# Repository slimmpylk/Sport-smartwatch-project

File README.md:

# Sportwatch

**A personal end-to-end smart/sport watch engineering project — custom electronics, PCB design, embedded software and system integration.**

This project is my attempt to design and build a complete sport-focused smartwatch from the ground up rather than assembling an existing development platform.

I am responsible for the full engineering workflow: component selection, datasheet analysis, schematic design, PCB architecture and layout, power design, sensor integration, RF-related design decisions, hardware bring-up, and eventually the embedded software running on the device.

> **Current phase:** hardware development. The schematic architecture is being designed in KiCad and the PCB will follow. Firmware and higher-level software development will begin as the hardware reaches the bring-up stage.

---

## Project goals

The goal is to build a compact wearable platform capable of supporting the core functions expected from a modern sport watch, while using the project as a practical system-level embedded engineering exercise.

The design includes:

- low-power application processor
- battery charging and power management
- AMOLED display
- GNSS
- inertial sensing
- magnetometer
- barometric pressure / altitude sensing
- temperature sensing
- ambient light sensing
- optical heart-rate / PPG hardware
- non-volatile storage
- haptic feedback
- wireless / RF subsystem
- physical buttons, charging and debug interfaces

The project is intentionally developed at component and PCB level rather than around a ready-made smartwatch module.

---

## Hardware architecture

| Subsystem | Main components / focus |
|---|---|
| Application processor | Ambiq Apollo510B |
| Power | Nordic nPM1300 PMIC |
| Display | RM69330-based round AMOLED |
| Motion | ST LSM6DSV16X IMU |
| Magnetometer | Bosch BMM350 |
| Pressure / altitude | Bosch BMP585 |
| Temperature | MAX30208 |
| Ambient light | OPT4001 |
| Optical sensing | MAX86140 / MAX86141 with discrete optical components |
| GNSS | u-blox MAX-F10S |
| Storage | eMMC |
| Haptics | TI DRV2625 |

Component choices and interfaces are verified against manufacturer datasheets as the design progresses.

### Display subsystem

Schematic excerpt for the round AMOLED display module interface (24-pin ZC-A1D43W-046 assembly): QSPI configuration, I²C touch controller, power rails and reset/enable circuitry:

---

## KiCad design organization

The schematic is divided into functional hierarchical sheets so each subsystem can be developed and reviewed independently.

```text
sportwatch_revA/
├── 01_APOLLO510B.kicad_sch
├── 02_POWER.kicad_sch
├── 03_DISPLAY.kicad_sch
├── 04_PPG.kicad_sch
├── 05_GNSS.kicad_sch
├── 06_WIFI.kicad_sch
├── 07_MOTION.kicad_sch
├── 08_ENVIRONMENT.kicad_sch
├── 09_STORAGE.kicad_sch
├── 10_HAPTICS.kicad_sch
├── 11_BUTTONS.kicad_sch
├── 12_CHARGING.kicad_sch
├── 13_DEBUG.kicad_sch
├── 14_RF.kicad_sch
├── sportwatch_revA.kicad_sch
├── sportwatch_revA.kicad_pcb
├── sportwatch_revA.kicad_pro
├── fp-lib-table
├── sym-lib-table
├── images/
│   └── display.jpg
└── libraries/
```

Custom symbols and footprints are kept with the project so the design remains portable between machines.

---

## Engineering focus

This project is primarily intended to demonstrate practical embedded hardware and system engineering, including:

- schematic capture and PCB design in **KiCad**
- reading and applying semiconductor datasheets
- component selection and interface design
- power-tree and battery-powered system design
- SPI / I²C and other digital interfaces
- mixed-signal sensor integration
- optical sensing / PPG subsystem design
- GNSS and RF integration
- decoupling, grounding and power-integrity considerations
- footprint verification against mechanical package drawings
- hierarchical schematic architecture
- hardware/software interface planning
- design validation before PCB manufacture
- Git-based engineering workflow and documentation

---

## Current development status

### Hardware

- [x] System architecture divided into functional schematic sheets
- [x] Initial power subsystem design
- [x] Application processor integration started
- [x] Motion-sensor integration
- [x] Custom symbols and footprints integrated where required
- [ ] Complete remaining schematic subsystems
- [ ] Full ERC and design review
- [ ] PCB placement
- [ ] PCB routing
- [ ] RF/layout review
- [ ] DRC and manufacturing review
- [ ] Prototype fabrication
- [ ] Hardware bring-up

### Software

Software development will follow the hardware bring-up phase.

Planned work includes:

- board-support and low-level drivers
- sensor acquisition
- power management
- display/UI integration
- GNSS handling
- activity and sport-related data processing
- storage
- device communications
- test and diagnostic tooling

The software side will be developed as part of the same project rather than treated as a separate pre-built platform.

---

## Development philosophy

The project is built around a simple principle: **understand and own the complete system**.

Rather than limiting the work to one layer, I want to work across the boundary between electronics and software — from component datasheets and PCB connectivity to low-level embedded code and final device behaviour.

That means the project evolves through the same stages as a real embedded product:

**requirements → architecture → schematic → PCB → prototype → bring-up → firmware → system integration → testing**

---

## Status

This repository is a work in progress and reflects an actively developed engineering project. The current focus is the PCB and electronics design phase, so incomplete sheets, un-routed PCB content and design changes are expected until the first hardware revision is finalized.

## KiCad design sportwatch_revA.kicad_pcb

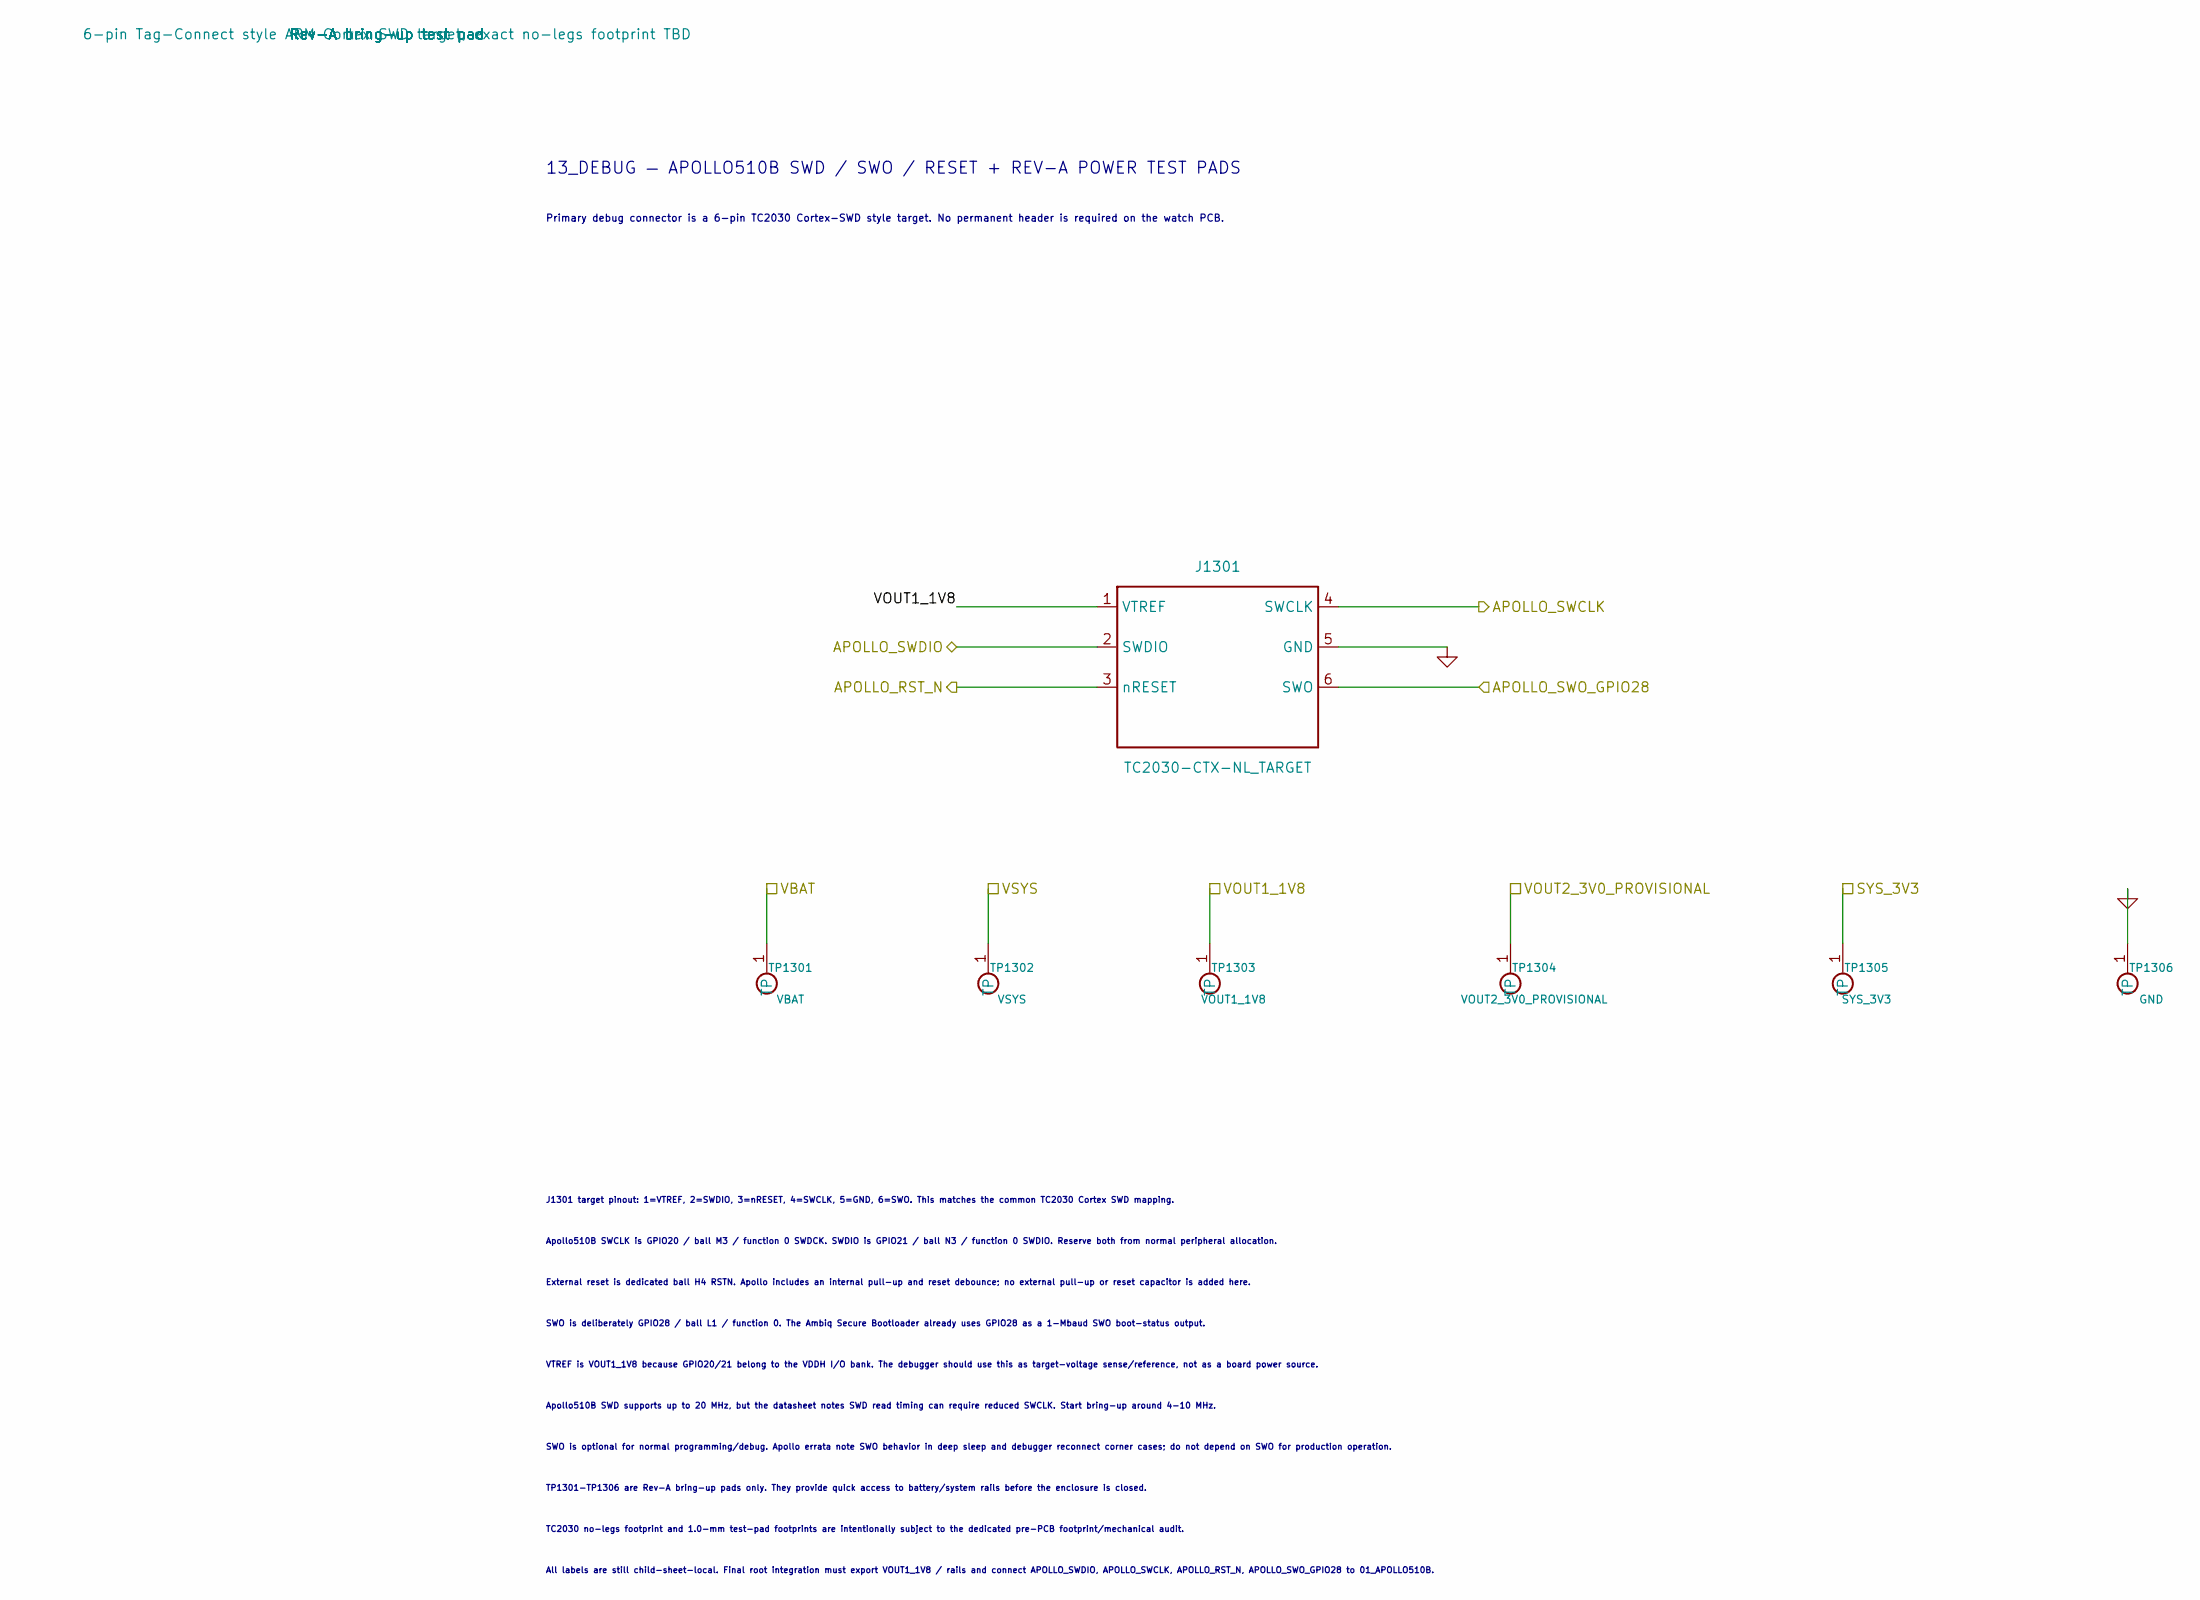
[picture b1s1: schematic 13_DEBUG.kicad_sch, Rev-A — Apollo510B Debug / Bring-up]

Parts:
J1301: TC2030-CTX-NL_TARGET; Tag-Connect_TC2030-IDC-NL_2x03_P1.27mm_Vertical
TP1301: VBAT; TestPoint_Pad_D1.0mm
TP1302: VSYS; TestPoint_Pad_D1.0mm
TP1303: VOUT1_1V8; TestPoint_Pad_D1.0mm
TP1304: VOUT2_3V0_PROVISIONAL; TestPoint_Pad_D1.0mm
TP1305: SYS_3V3; TestPoint_Pad_D1.0mm
TP1306: GND; TestPoint_Pad_D1.0mm

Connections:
/APOLLO_RST_N: J1301.3 (nRESET); also elsewhere on the board
/APOLLO_SWCLK: J1301.4 (SWCLK); also elsewhere on the board
/APOLLO_SWDIO: J1301.2 (SWDIO); also elsewhere on the board
/APOLLO_SWO_GPIO28: J1301.6 (SWO); also elsewhere on the board
/SYS_3V3: TP1305.1 (TP_1); also elsewhere on the board
/VOUT2_3V0_PROVISIONAL: TP1304.1 (TP_1); also elsewhere on the board
/VSYS: TP1302.1 (TP_1); also elsewhere on the board
GND: J1301.5 (GND), TP1306.1 (TP_1); also elsewhere on the board
VBAT: TP1301.1 (TP_1); also elsewhere on the board
VOUT1_1V8: J1301.1 (VTREF), TP1303.1 (TP_1); also elsewhere on the board

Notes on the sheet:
J1301 target pinout: 1=VTREF, 2=SWDIO, 3=nRESET, 4=SWCLK, 5=GND, 6=SWO. This matches the common TC2030 Cortex SWD mapping.
13_DEBUG — APOLLO510B SWD / SWO / RESET + REV-A POWER TEST PADS
SWO is optional for normal programming/debug. Apollo errata note SWO behavior in deep sleep and debugger reconnect corner cases; do not depend on SWO for production operation.
VTREF is VOUT1_1V8 because GPIO20/21 belong to the VDDH I/O bank. The debugger should use this as target-voltage sense/reference, not as a board power source.
All labels are still child-sheet-local. Final root integration must export VOUT1_1V8 / rails and connect APOLLO_SWDIO, APOLLO_SWCLK, APOLLO_RST_N, APOLLO_SWO_GPIO28 to 01_APOLLO510B.
Apollo510B SWCLK is GPIO20 / ball M3 / function 0 SWDCK. SWDIO is GPIO21 / ball N3 / function 0 SWDIO. Reserve both from normal peripheral allocation.
TC2030 no-legs footprint and 1.0-mm test-pad footprints are intentionally subject to the dedicated pre-PCB footprint/mechanical audit.
External reset is dedicated ball H4 RSTN. Apollo includes an internal pull-up and reset debounce; no external pull-up or reset capacitor is added here.
SWO is deliberately GPIO28 / ball L1 / function 0. The Ambiq Secure Bootloader already uses GPIO28 as a 1-Mbaud SWO boot-status output.
Apollo510B SWD supports up to 20 MHz, but the datasheet notes SWD read timing can require reduced SWCLK. Start bring-up around 4-10 MHz.
Primary debug connector is a 6-pin TC2030 Cortex-SWD style target. No permanent header is required on the watch PCB.
TP1301-TP1306 are Rev-A bring-up pads only. They provide quick access to battery/system rails before the enclosure is closed.

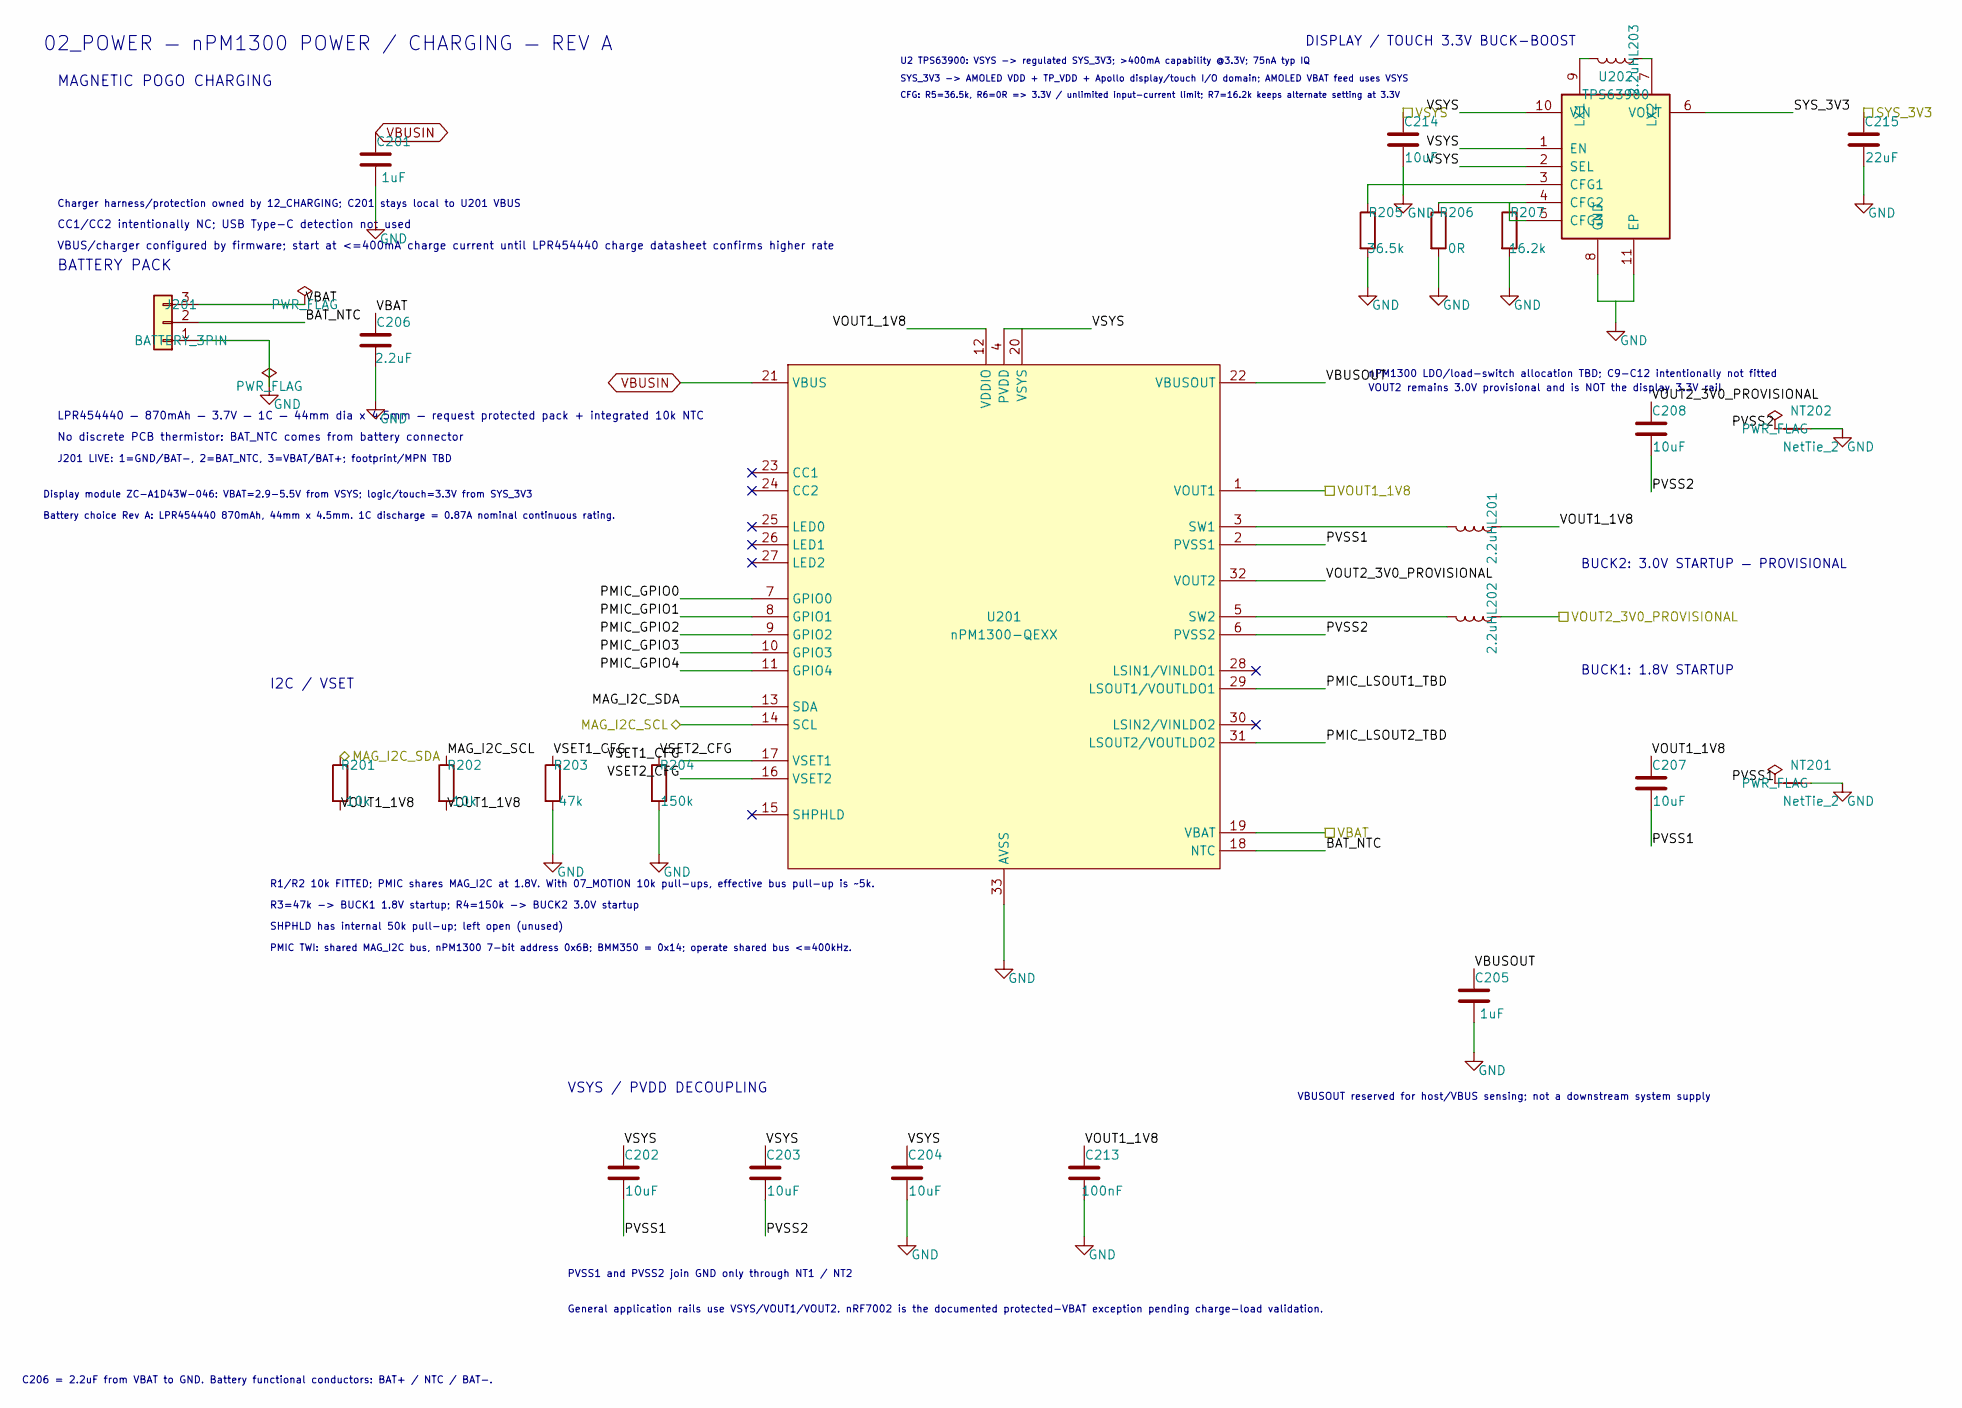
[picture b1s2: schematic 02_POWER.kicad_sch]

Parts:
C201, C205: 1uF; C_0402_1005Metric
C202, C203, C204, C207, C208, C214: 10uF; C_0603_1608Metric
C206: 2.2uF; C_0402_1005Metric
C213: 100nF; C_0402_1005Metric
C215: 22uF; C_0603_1608Metric
J201: BATTERY_3PIN
L201, L202: 2.2uH; L_0603_1608Metric
L203: 2.2uH; L_2016_2016Metric
NT201, NT202: NetTie_2; NetTie-2_SMD_Pad0.5mm
R201, R202: 10k; R_0402_1005Metric
R203: 47k; R_0402_1005Metric; Tolerance 1%
R204: 150k; R_0402_1005Metric; Tolerance 1%
R205: 36.5k; R_0402_1005Metric; Tolerance 1%
R206: 0R; R_0402_1005Metric; Tolerance 1%
R207: 16.2k; R_0402_1005Metric; Tolerance 1%
U201: nPM1300-QEXX; QFN-32-1EP_5x5mm_P0.5mm_EP3.6x3.6mm_ThermalVias
U202: TPS63900; WSON-10-1EP_2.5x2.5mm_P0.5mm_EP1.2x2mm_ThermalVias; MPN TPS63900DSK

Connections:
/02_POWER/BAT_NTC: J201.2, U201.18 (NTC)
/02_POWER/PMIC_GPIO0: U201.7 (GPIO0)
/02_POWER/PMIC_GPIO1: U201.8 (GPIO1)
/02_POWER/PMIC_GPIO2: U201.9 (GPIO2)
/02_POWER/PMIC_GPIO3: U201.10 (GPIO3)
/02_POWER/PMIC_GPIO4: U201.11 (GPIO4)
/02_POWER/PMIC_LSOUT1_TBD: U201.29 (LSOUT1/VOUTLDO1)
/02_POWER/PMIC_LSOUT2_TBD: U201.31 (LSOUT2/VOUTLDO2)
/02_POWER/PVSS1: C202.2, C207.2, NT201.1, U201.2 (PVSS1)
/02_POWER/PVSS2: C203.2, C208.2, NT202.1, U201.6 (PVSS2)
/02_POWER/VBUSOUT: C205.1, U201.22 (VBUSOUT)
/02_POWER/VSET1_CFG: R203.1, U201.17 (VSET1)
/02_POWER/VSET2_CFG: R204.1, U201.16 (VSET2)
/MAG_I2C_SCL: R202.1, U201.14 (SCL); also elsewhere on the board
/MAG_I2C_SDA: R201.1, U201.13 (SDA); also elsewhere on the board
/SYS_3V3: C215.1, U202.6 (VOUT); also elsewhere on the board
/VOUT2_3V0_PROVISIONAL: C208.1, L202.1, U201.32 (VOUT2); also elsewhere on the board
/VSYS: C202.1, C203.1, C204.1, C214.1, U201.4 (PVDD), U201.20 (VSYS), U202.1 (EN), U202.2 (SEL), U202.10 (VIN); also elsewhere on the board
GND: C201.2, C204.2, C205.2, C206.2, C213.2, C214.2, C215.2, J201.1, NT201.2, NT202.2, R203.2, R204.2, R205.2, R206.2, R207.2, U201.33 (AVSS), U202.8 (GND), U202.11 (EP); also elsewhere on the board
unnamed: L201.2, U201.3 (SW1)
unnamed: L202.2, U201.5 (SW2)
unnamed: R205.1, U202.3 (CFG1)
unnamed: R206.1, U202.4 (CFG2)
unnamed: R207.1, U202.5 (CFG3)
unnamed: L203.2, U202.9 (LX1)
unnamed: L203.1, U202.7 (LX2)
VBAT: C206.1, J201.3, U201.19 (VBAT); also elsewhere on the board
VBUSIN: C201.1, U201.21 (VBUS)
VOUT1_1V8: C207.1, C213.1, L201.1, R201.2, R202.2, U201.1 (VOUT1), U201.12 (VDDIO); also elsewhere on the board

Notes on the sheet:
VBUSOUT reserved for host/VBUS sensing; not a downstream system supply
U2 TPS63900: VSYS -> regulated SYS_3V3; >400mA capability @3.3V; 75nA typ IQ
Battery choice Rev A: LPR454440 870mAh, 44mm x 4.5mm. 1C discharge = 0.87A nominal continuous rating.
BATTERY PACK
DISPLAY / TOUCH 3.3V BUCK-BOOST
SYS_3V3 -> AMOLED VDD + TP_VDD + Apollo display/touch I/O domain; AMOLED VBAT feed uses VSYS
Charger harness/protection owned by 12_CHARGING; C201 stays local to U201 VBUS
VSYS / PVDD DECOUPLING
BUCK1: 1.8V STARTUP
CFG: R5=36.5k, R6=0R => 3.3V / unlimited input-current limit; R7=16.2k keeps alternate setting at 3.3V
No discrete PCB thermistor: BAT_NTC comes from battery connector
CC1/CC2 intentionally NC; USB Type-C detection not used
R3=47k -> BUCK1 1.8V startup; R4=150k -> BUCK2 3.0V startup
I2C / VSET
nPM1300 LDO/load-switch allocation TBD; C9-C12 intentionally not fitted
02_POWER — nPM1300 POWER / CHARGING — REV A
LPR454440 — 870mAh — 3.7V — 1C — 44mm dia x 4.5mm — request protected pack + integrated 10k NTC
R1/R2 10k FITTED; PMIC shares MAG_I2C at 1.8V. With 07_MOTION 10k pull-ups, effective bus pull-up is ~5k.
MAGNETIC POGO CHARGING
J201 LIVE: 1=GND/BAT-, 2=BAT_NTC, 3=VBAT/BAT+; footprint/MPN TBD
Display module ZC-A1D43W-046: VBAT=2.9-5.5V from VSYS; logic/touch=3.3V from SYS_3V3
SHPHLD has internal 50k pull-up; left open (unused)
VBUS/charger configured by firmware; start at <=400mA charge current until LPR454440 charge datasheet confirms higher rate
VOUT2 remains 3.0V provisional and is NOT the display 3.3V rail
PVSS1 and PVSS2 join GND only through NT1 / NT2
BUCK2: 3.0V STARTUP — PROVISIONAL
General application rails use VSYS/VOUT1/VOUT2. nRF7002 is the documented protected-VBAT exception pending charge-load validation.
PMIC TWI: shared MAG_I2C bus, nPM1300 7-bit address 0x6B; BMM350 = 0x14; operate shared bus <=400kHz.
C206 = 2.2uF from VBAT to GND. Battery functional conductors: BAT+ / NTC / BAT-.

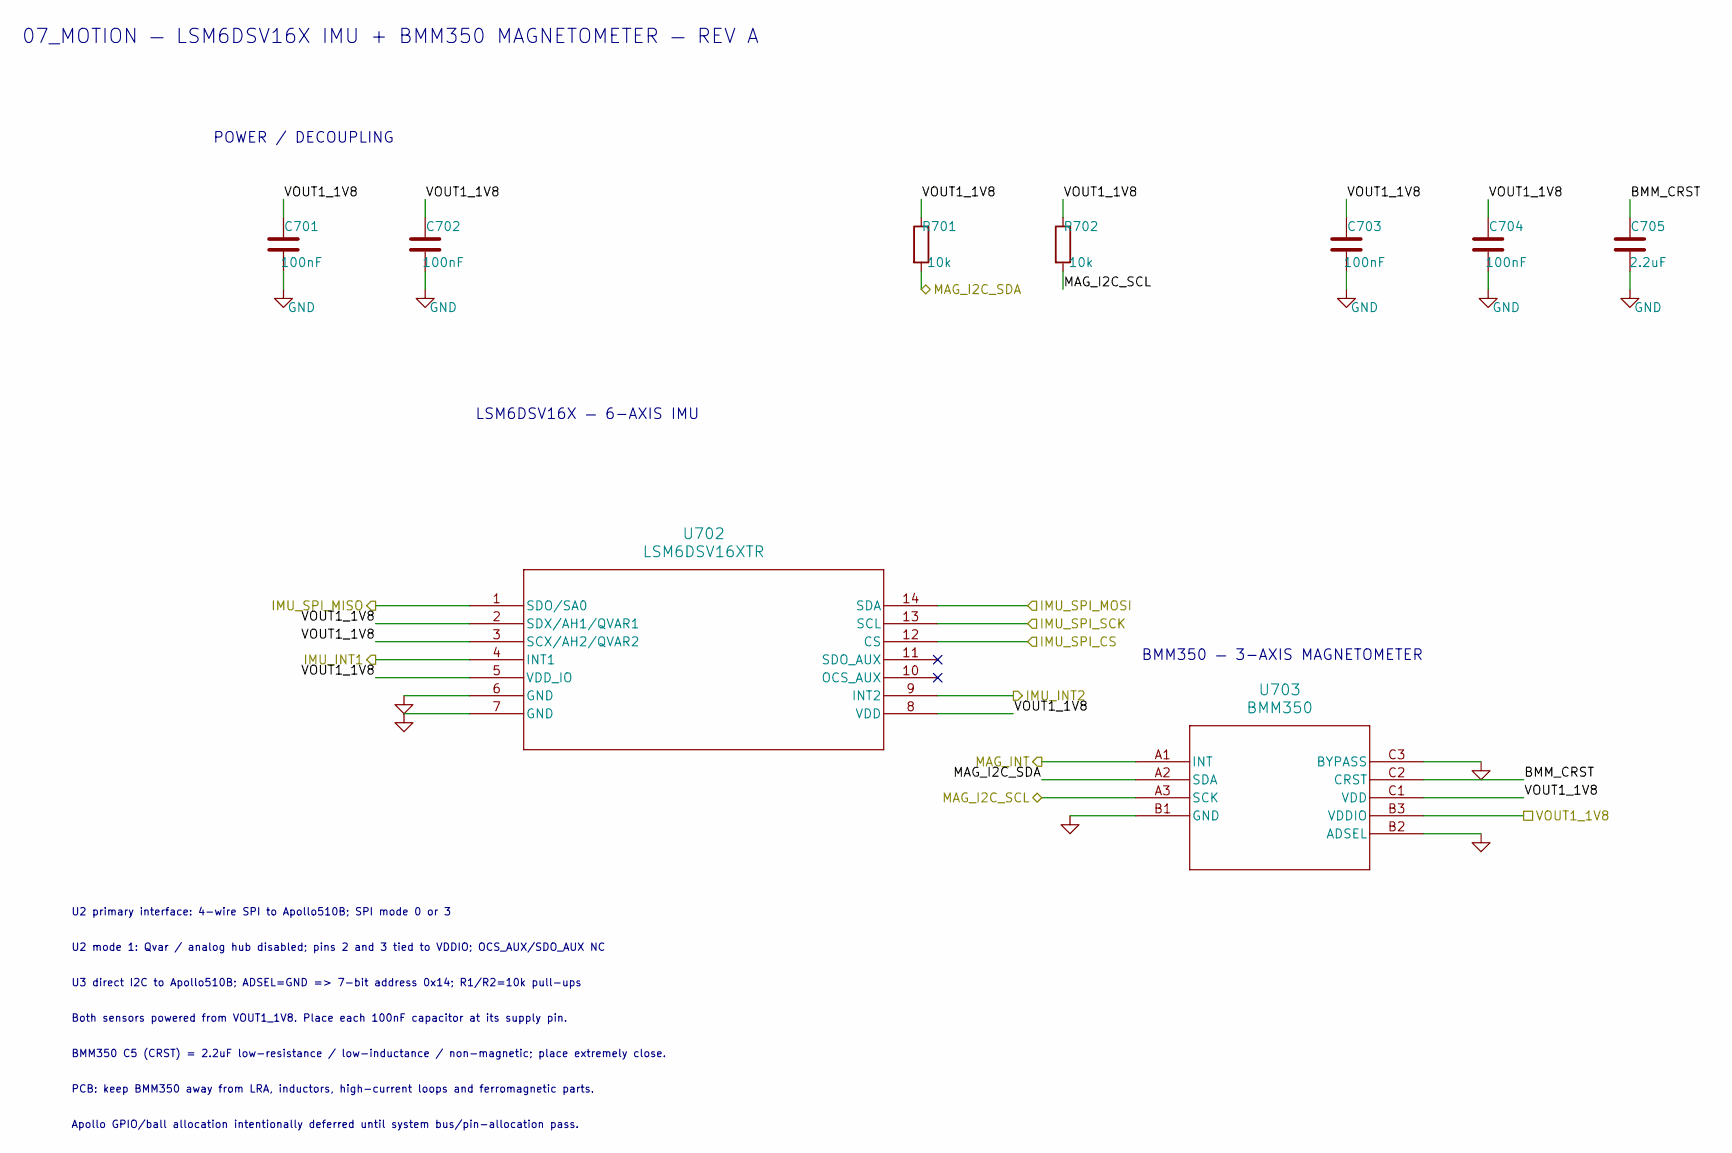
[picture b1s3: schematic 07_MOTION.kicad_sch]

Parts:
C701, C702, C703, C704: 100nF; C_0402_1005Metric
C705: 2.2uF; C_0805_2012Metric
R701, R702: 10k; R_0402_1005Metric; Tolerance 1%
U702: LSM6DSV16XTR; LGA-14L_STM
U703: BMM350; BGA9_BMM350_BOS

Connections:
/07_MOTION/BMM_CRST: C705.1, U703.C2 (CRST)
/IMU_INT1: U702.4 (INT1); also elsewhere on the board
/IMU_INT2: U702.9 (INT2); also elsewhere on the board
/IMU_SPI_CS: U702.12 (CS); also elsewhere on the board
/IMU_SPI_MISO: U702.1 (SDO/SA0); also elsewhere on the board
/IMU_SPI_MOSI: U702.14 (SDA); also elsewhere on the board
/IMU_SPI_SCK: U702.13 (SCL); also elsewhere on the board
/MAG_I2C_SCL: R702.2, U703.A3 (SCK); also elsewhere on the board
/MAG_I2C_SDA: R701.2, U703.A2 (SDA); also elsewhere on the board
/MAG_INT: U703.A1 (INT); also elsewhere on the board
GND: C701.2, C702.2, C703.2, C704.2, C705.2, U702.6 (GND), U702.7 (GND), U703.B1 (GND), U703.B2 (ADSEL), U703.C3 (BYPASS); also elsewhere on the board
VOUT1_1V8: C701.1, C702.1, C703.1, C704.1, R701.1, R702.1, U702.2 (SDX/AH1/QVAR1), U702.3 (SCX/AH2/QVAR2), U702.5 (VDD_IO), U702.8 (VDD), U703.B3 (VDDIO), U703.C1 (VDD); also elsewhere on the board

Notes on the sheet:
LSM6DSV16X — 6-AXIS IMU
BMM350 C5 (CRST) = 2.2uF low-resistance / low-inductance / non-magnetic; place extremely close.
BMM350 — 3-AXIS MAGNETOMETER
U2 primary interface: 4-wire SPI to Apollo510B; SPI mode 0 or 3
U2 mode 1: Qvar / analog hub disabled; pins 2 and 3 tied to VDDIO; OCS_AUX/SDO_AUX NC
07_MOTION — LSM6DSV16X IMU + BMM350 MAGNETOMETER — REV A
U3 direct I2C to Apollo510B; ADSEL=GND => 7-bit address 0x14; R1/R2=10k pull-ups
POWER / DECOUPLING
PCB: keep BMM350 away from LRA, inductors, high-current loops and ferromagnetic parts.
Apollo GPIO/ball allocation intentionally deferred until system bus/pin-allocation pass.
Both sensors powered from VOUT1_1V8. Place each 100nF capacitor at its supply pin.

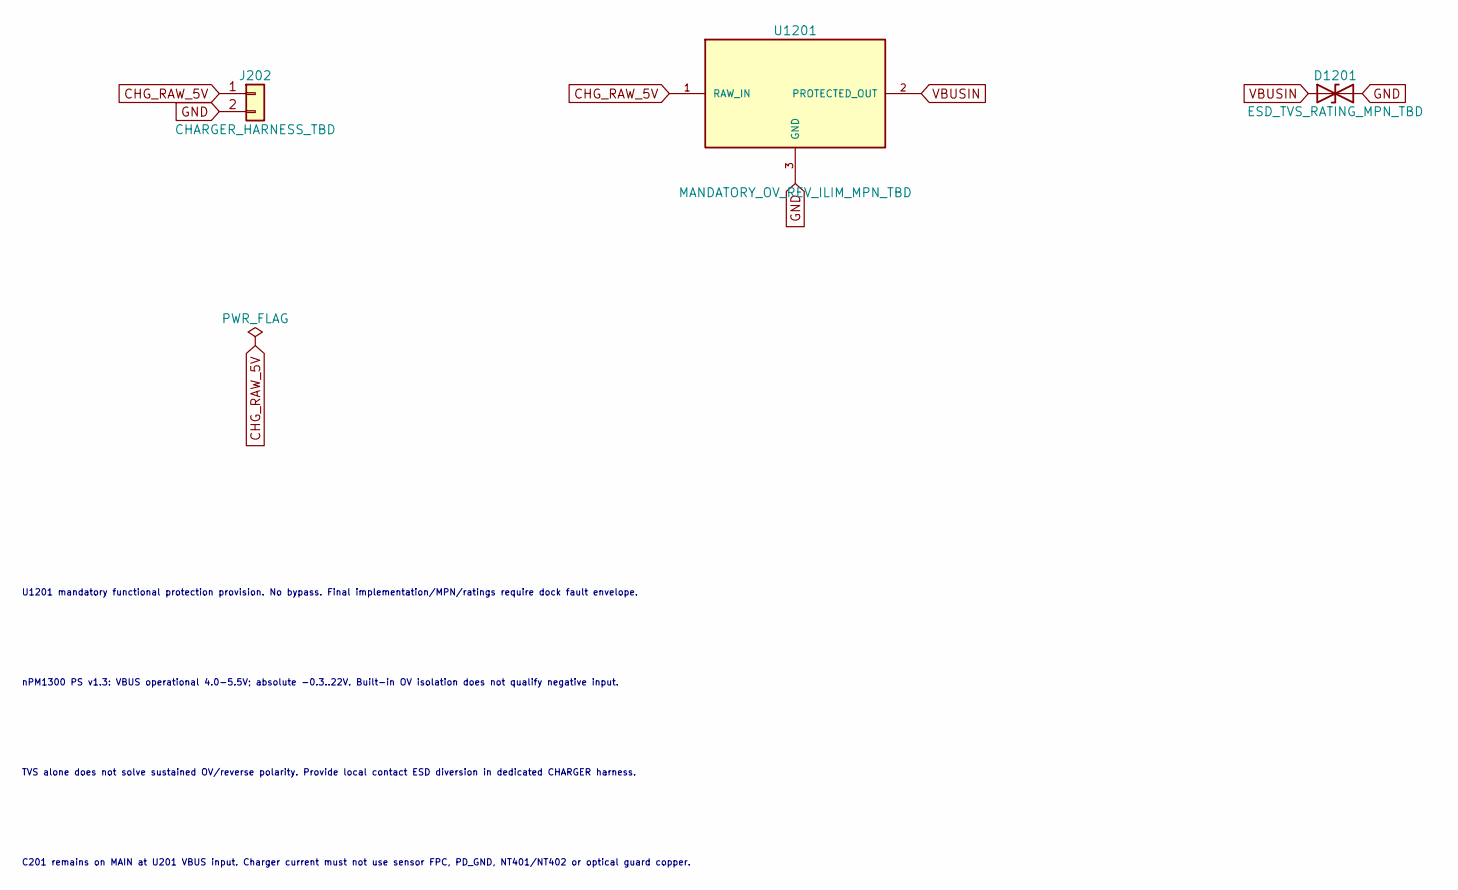
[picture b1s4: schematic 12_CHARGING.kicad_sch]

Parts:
D1201: ESD_TVS_RATING_MPN_TBD
J202: CHARGER_HARNESS_TBD
U1201: MANDATORY_OV_REV_ILIM_MPN_TBD

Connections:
unnamed: D1201.1 (A1), U1201.2 (PROTECTED_OUT)
unnamed: D1201.2 (A2), J202.2, U1201.3 (GND)
unnamed: J202.1, U1201.1 (RAW_IN)

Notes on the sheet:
U1201 mandatory functional protection provision. No bypass. Final implementation/MPN/ratings require dock fault envelope.
nPM1300 PS v1.3: VBUS operational 4.0-5.5V; absolute -0.3..22V. Built-in OV isolation does not qualify negative input.
TVS alone does not solve sustained OV/reverse polarity. Provide local contact ESD diversion in dedicated CHARGER harness.
C201 remains on MAIN at U201 VBUS input. Charger current must not use sensor FPC, PD_GND, NT401/NT402 or optical guard copper.
